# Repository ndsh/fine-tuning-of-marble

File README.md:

# floorScanners
Repository for the source code of an ongoing sound installation and performance. It was first presented at Resonate Festival in 2016 in its prototyped Version we called "Fine Tuning of Marble".

## Overview
* [Dependencies](#dependencies)
* [About](#about)
* [Classes](#classes)
* [PCB](#pcb)
* [Authors](#authors)

---

### About
tbd

---

### Dependencies
* [AccelStepper Library, v1.51](http://www.airspayce.com/mikem/arduino/AccelStepper/)
* [Teensy MIDI, v3.2](https://www.pjrc.com/teensy/td_libs_MIDI.html)

---

### Classes

These are the primary classes of the floorScanners living inside the /src/ folder

| Classname         | Description                                   | No. of Methods    | Current working state |
|-------------------|-----------------------------------------------|-------------------|-----------------------|
| StateMachine      | Organize States of a floorScanner             | 4/4               | Working               |
| Clock             | Synchronize Scanners with a pulse             | N/A               | Deprecated (?)        |
| Motor             | Control Stepper Motor / Acceleration et al    | 11/11             | Working               |
| Score             | -                                             | N/A               | Deprecated (?)        |
| SensorHead        | Reading and storing sensordata on a circle    | 4/7               | Working               |
| Synth             | Synth output over speakers. Adjust timber etc | N/A               | Working               |
| Communication     | Communication between Scanners over MIDI      | N/A               | Not working yet       |
| MacAddress        | Returns a Teensy MacAddress                   | 2/2               | Working               |

<br>

These are secondary classes from the [Automatic Orchestra Library](https://github.com/automatic-orchestra/ao_library) and live next to the primary classes in the /src/ folder.
They have been copied over from the latest release and are basically version frozen as of now

| Classname         | Description                                   | No. of Methods    | Current working state |
|-------------------|-----------------------------------------------|-------------------|-----------------------|
| CFOSynthesizer    | CheapFatOpen Synth parts to control the DAC   | ?                 | Working               |
| CFOMidi           | Send/Receive MIDI on the Teensy               | ?                 | Working               |

---

### PCB
Revisions
- [ ] Redesign the PCB stack into a single square board
- [ ] DRV8825 M0, M1, M2 to Pins
- [ ] Integrate TDA2030 circuit
- [ ] Switch terminal blocks with WAGO 2060 SMD
- [ ] Integrate PROTOSEQ circuit
- [ ] Expose all available pins
- [ ] Re-examine the audio interface between PROTOSEQ and TDA2030 (Is it really necessary to have the TDA2030?)

---

#### Authors
<sub>

Copyright (c) 2016 – 2021 (The Fine Tuning of Marble / floorScanners)
- &nearr; [Irena Kukric](https://www.irenakukric.com)
- &nearr; [Luiz Zanotello](https://www.luizzanotello.com)
- &nearr; [Julian Hespenheide](https://www.julian-h.de)

</sub>

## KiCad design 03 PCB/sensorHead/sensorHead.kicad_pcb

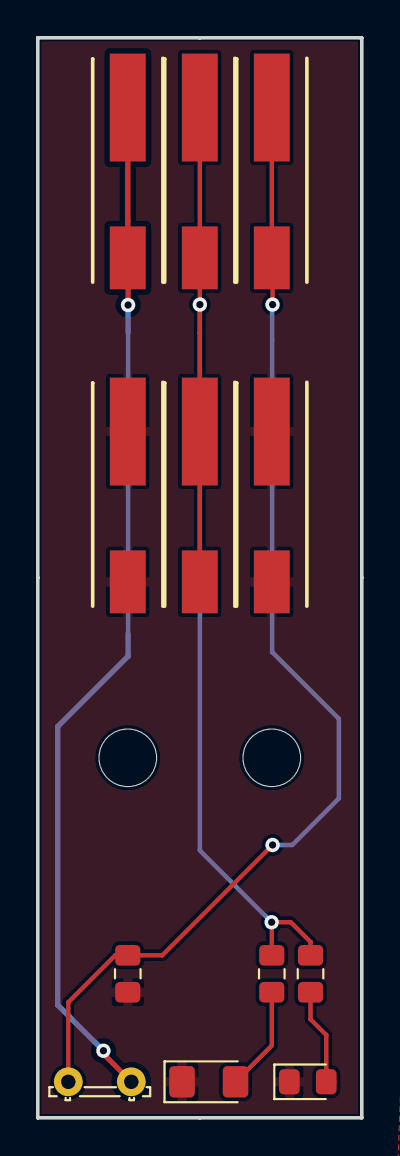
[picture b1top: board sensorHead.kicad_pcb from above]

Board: 2 copper layers, 18.0 x 60.0 mm, 12 parts (0 on the bottom side), 6 nets.

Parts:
D1: LED MAIN; LED_1206_3216Metric_Pad1.42x1.75mm_HandSolder
D2: LED MAIN; LED_0805_2012Metric_Pad1.15x1.40mm_HandSolder
J1: WAGO 1; WAGOSMD_p_2060_451_aktualisiert
J2: WAGO 2; WAGOSMD_p_2060_451_aktualisiert
J3: WAGO 3; WAGOSMD_p_2060_451_aktualisiert
J4: WAGO 4; WAGOSMD_p_2060_451_aktualisiert
J5: WAGO 5; WAGOSMD_p_2060_451_aktualisiert
J6: WAGO 8; WAGOSMD_p_2060_451_aktualisiert
LDR1: D_Photo; R_LDR_5.2x5.2mm_P3.5mm_Horizontal
R1: 10k; R_0805_2012Metric_Pad1.15x1.40mm_HandSolder
R2, R3: 68 Ohm; R_0805_2012Metric_Pad1.15x1.40mm_HandSolder

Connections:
+5V: J1.1, J1.2, LDR1.1
GND: D1.1, D2.1, J5.1, J5.2, J6.1, J6.2, R1.1
LDR_ANALOG: J3.1, J3.2, LDR1.2, R1.2
LED_MAIN: J2.1, J2.2, J4.1, J4.2, R2.1, R3.1
unnamed: D1.2, R2.2
unnamed: D2.2, R3.2

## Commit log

2016-05-29 Main Structure
    Defined and initialized main classes and headers. Defined main update structure. Defined PINs. Updated the README file.
2016-05-29 README update
    Updated the README.md file.
2016-05-29 README Update
    Updated the version and link to the AccelStepper Library.
2016-06-03 FTSensor implementation + FTMotor development
    Implemented initial state for the FTSensor class. Updated FTMotor. Instantiated motor to start programming its movement functions.
2016-06-03 FCMotor update
    Initiated the development of the main functions.
2016-06-17 FTMotor update: speed functions & position control
    Finalized speeding functions. Finalized position conversion functions. Updated minor semantics of variables and functions. Still missing: bux fix of CCW runTo(), and callback functions.
2016-07-08 FTMotor Improvements
    Fixed the bug on forcing negative rotations, debuged, improved, and tested all the functions for movement and speed control. Included an example of usage inside FTPod. Included DEBUG messages.
2016-07-08 FTPod Structuring
    Set up basic watching & updating functions for the main FTPod class. Upated the name of the DEBUG bool (general).
2016-07-15 FULLREV Update
    Updated FULLREV value to a "global" definition, instead of contained within FTMotor. Started the implementation of FTSensor.
2016-07-15 FTSensor Implementation + General updates
    Implemented the sensor parsing, and filtering basic functions (needs testing together with motor functions). Updated full revolution value. Updated DEBUG functions.
2016-07-22 FTSensor Update
    Updated getDataFromAbsolutePos() to return the data value related to the closest absolutePos.
2016-07-22 FTMotor Update
    Included functions to get and convert the current absolute and relative positions of the motor.
2016-07-22 FTMotor Update
    Fixed a few bugs on negative forced direction, updated the getCurrentAbsolutePosition to return only from 0 to fullRev (instead of -fullRev to fullRev), and included/updated debug messages.
2016-07-22 gitignore update
2016-07-22 little annotation on FTCom
    it might best to dump all the AO midi stuff, since we control our installation *fundamentally* different
2016-07-22 FTPod: macAddresses + Music
    - void retrieveMacAdress() gets the teensy's MAC and stores in a variable AKA setMacAdress()
    - String getMacAdresses() returns the MAC
    - on Constructor of FTPod a small jingle plays to ensure that the Synthesizer is enabled, alive and well running!
2016-07-22 FTSensor Update + FTPod Update
2016-07-28 FTPod Update
2016-07-29 FTPod: removed merge markings
2016-07-29 added digital pin: PODZERO
    if left with no SPDT switch, it pulls low
2016-07-29 FTClock Implementation + FTPod Update
    Implemented FTClock pulse functions, and updated FTPod accordingly to update the clock. Also made minor semantic changes on the button pin.
2016-07-30 podZero
2016-07-30 pinMode: START_PIN
    i think it should be pulled down instead of a floating pin. so we don't have to put any more redundant resistors on the pcbs
2016-08-09 FTPod + FTSynth + FTCom Update
    Moved different functions instantiated inside FTPod or at the main .ino to their respective classes (mac address control to FTCom, music init at FTSynth, podZero check to FTPod).
2016-08-09 Score Implementation + FTPod + FTClock + FTCom Upd
    Implemented the system for controlling the current act and composition in play. Deleted FTScore due to simplified structure to manipulate the acts. Updated FTPod, FTClock, FTCom and the main .ino wit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
2016-08-12 FTCom Update
2016-08-12 FTClock + FTPod Update
    pulseIn(), pulseOut(), readPulse() and updatePulse() updated.
2016-08-12 FTCom: pulse methods
2016-08-12 FTPod Update
    Updated receiveCom() to set the master and start the play and pulse sending
2016-08-13 App+FTPod+FTCom: OnBoard LED for communication
2016-08-13 FTCom: added read/write methods
2016-08-16 Monitor output changes + MAC + FTCom + notation
    - Monitor output changes are mostly of cosmetic nature and range from changing (at least for now) a few headers (comment style) to something bit lighter
    - a new unified *approach* for terminal outputs. let's see how this goes during development
    - MAC addresses moved back into FTPod: the Pod should know what his sub-routines are (delegate data between them) and should be the highest instance of them to identify itself in the network (therefo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
    - FTCom: raw implementations of read()/write(). write() is overloaded, so we can either send all channels or just a specific channel
    - notation: trying to establi
2016-08-16 added inc/Hardware.h
    due to complications with the MIDI protocol, Hardware IDs of Teensies should be collected in Hardware.h
    these will be read once by FTPod.h in order to find out, which channel id the pod has.
    in the end it doesn't matter if podZero is actually channel 0 or channel 1-6
2016-08-16 mishap in naming MIDI methods
    eg.
    sendControlChange = name of method
    controlChange = the actual string that can be received and processed via a switch-case
2016-08-17 full sweep on notation + terminal outputs
2016-08-19 FTSynth: Implementation
    Implemented applyPreset(...), mapDataToNote(...) and playNote(...) methods. Implemented also the possibility of scalling (see parameters and comments).
2016-08-22 FTScore + FTAct: Basic Implementation
    Implemented basic classes for managing the acts and the Score. Needs integration to the FTPod and already programmed methods. Updated/optmizied a few things at FTPod, .ino, Clock and Synth.
2016-08-29 FTScore + FTAct Update
    Current act id is now stored at FTPod, which communicates to the FTScore to get/update the states of each act. Also corrected semantic errors.
2016-08-29 FTScore management implementation
    Implemented the methods for managing FTScore within FTPod. Updated several methods and implemented new ones in supporting classes to accommodate better the new Score structure. Also made minor improv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
2017-03-31 Processing Simulation
    Simulation V01 Complete. See floorscanners_simulation.pde for details on how to edit it.
2021-05-28 readme update
2021-05-28 remove old
2021-05-28 add arduino
    old stable version from luiz
    new module tests for getting started in 2021
2021-05-28 processing sim from luiz
2021-05-28 it is all about the pcbs
    HELLOxPROTO PCB, 2016
    sensorHead, 2020
2021-05-28 readme
2021-05-28 naming scheme of folders
2021-05-28 rename because of subcommit
2021-05-28 re-rename of the subcommit :)
2021-05-28 removed PCB out
2021-05-28 ignore update
2021-05-28 rename of sensorHead folder
2021-05-28 ignore
2021-05-28 removed some git update stream / stashed changes
    but code is still not runnable and probably won’t be for some time
2021-05-28 floorScanner dev
    taking things from old FTM app and integrate it into new floorScanner app with a stateMachine encapsulating the whole fun
2021-05-29 updatooo
2021-05-29 it compiles
2021-05-30 going forward
2021-06-01 update some stuff
